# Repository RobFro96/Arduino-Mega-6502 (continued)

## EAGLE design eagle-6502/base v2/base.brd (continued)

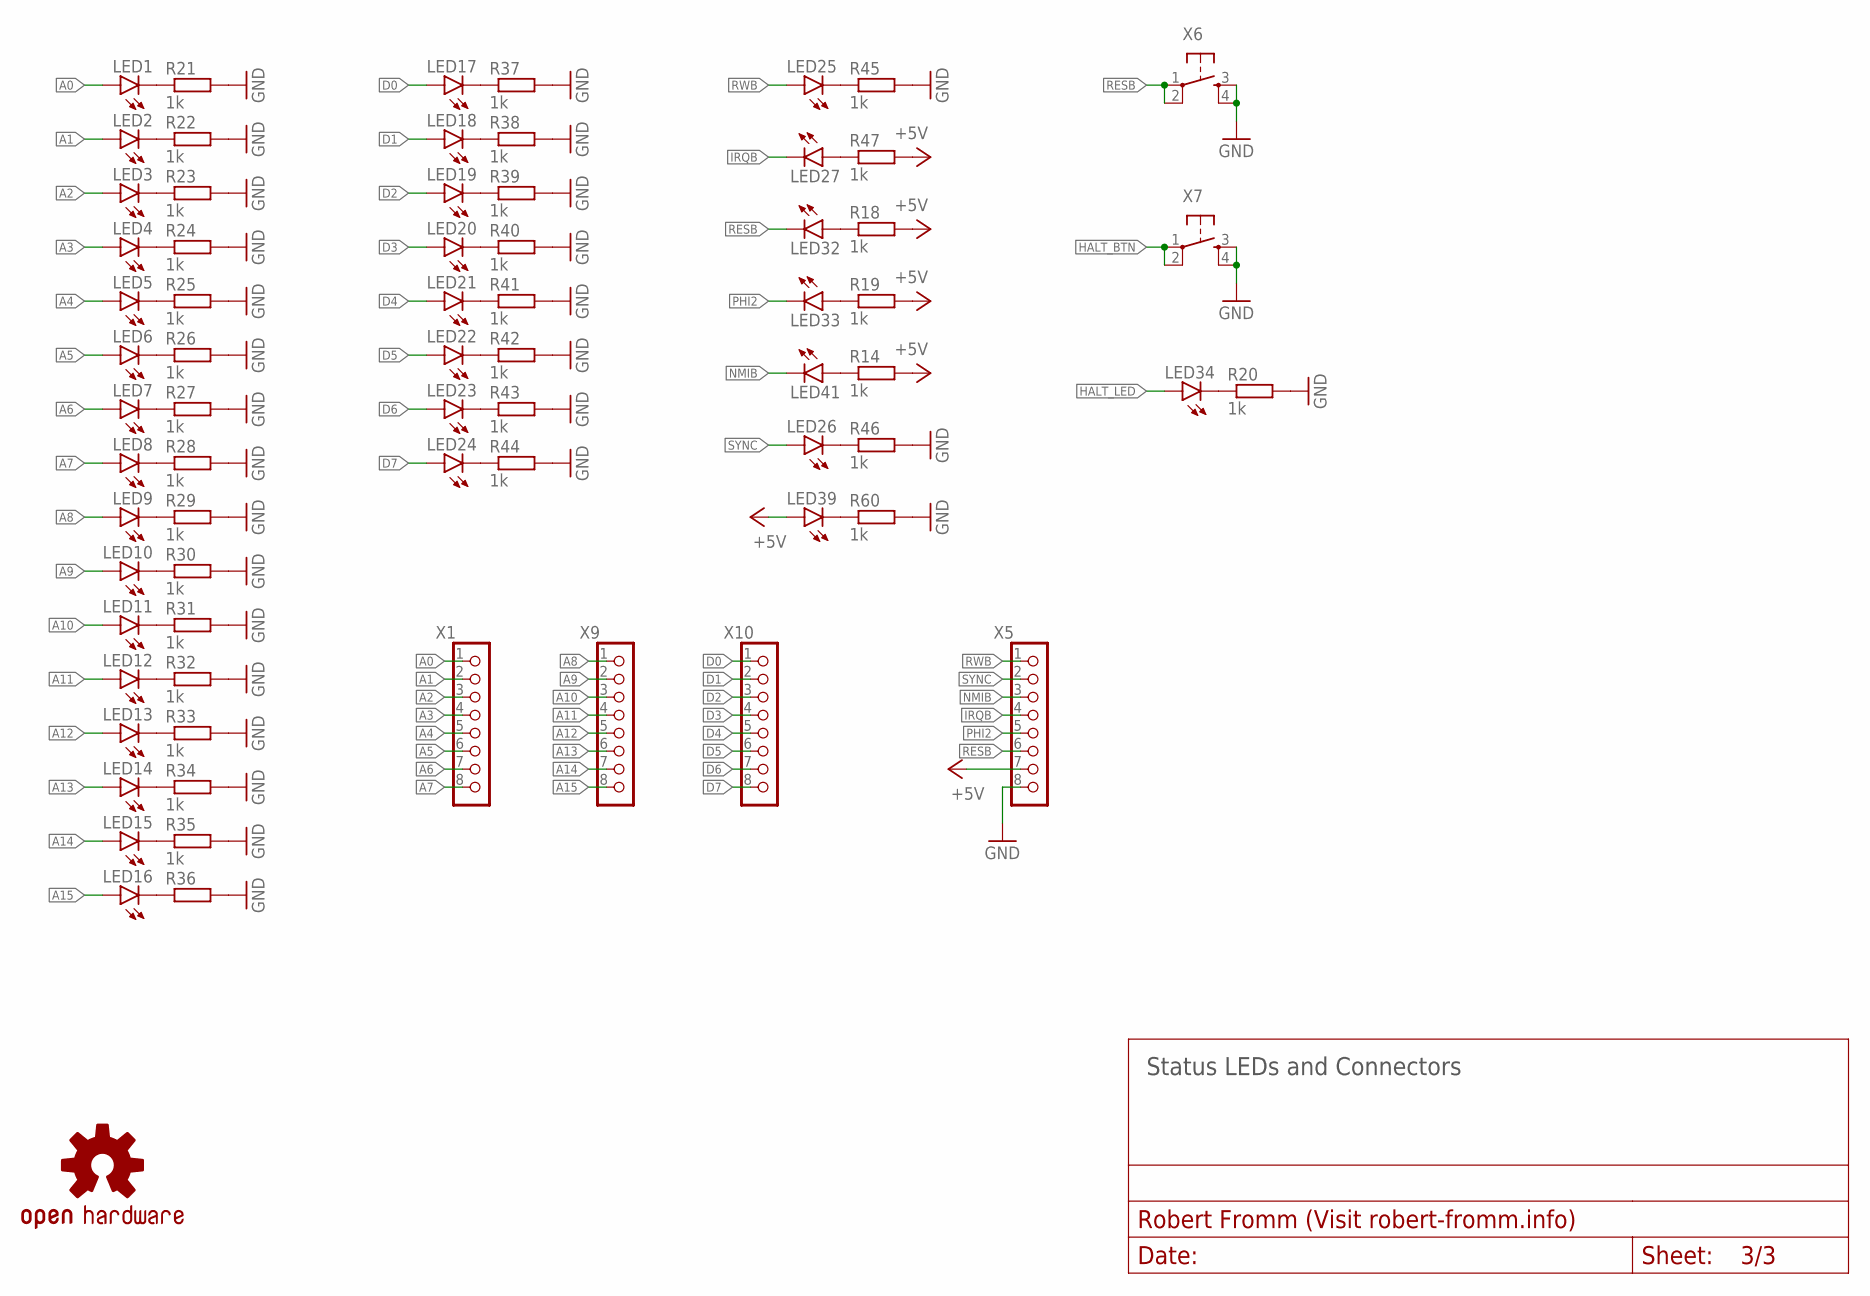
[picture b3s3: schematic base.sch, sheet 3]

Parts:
LED1, LED2, LED3, LED4, LED5, LED6, LED7, LED8, LED9, LED10, LED11, LED12, LED13, LED14, LED15, LED16, LED17, LED18, LED19, LED20, LED21, LED22, LED23, LED24, LED25, LED26, LED27, LED32, LED33, LED34, LED39, LED41: LEDSML0805; SML0805
LOGO1: OSHW-LOGOM; OSHW-LOGO-M
R14, R18, R19, R20, R21, R22, R23, R24, R25, R26, R27, R28, R29, R30, R31, R32, R33, R34, R35, R36, R37, R38, R39, R40, R41, R42, R43, R44, R45, R46, R47, R60: 1k; R0805
X1, X5, X9, X10: PINHD_8_RND; 1X08
X6, X7: TACT_SWITCH; TACTILE_SWITCH_PTH_6.0MM

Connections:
+5V: LED39.A, R14.2, R18.2, R19.2, R47.2, X5.7; also elsewhere on the board
A0: LED1.A, X1.1; also elsewhere on the board
A1: LED2.A, X1.2; also elsewhere on the board
A2: LED3.A, X1.3; also elsewhere on the board
A3: LED4.A, X1.4; also elsewhere on the board
A4: LED5.A, X1.5; also elsewhere on the board
A5: LED6.A, X1.6; also elsewhere on the board
A6: LED7.A, X1.7; also elsewhere on the board
A7: LED8.A, X1.8; also elsewhere on the board
A8: LED9.A, X9.1; also elsewhere on the board
A9: LED10.A, X9.2; also elsewhere on the board
A10: LED11.A, X9.3; also elsewhere on the board
A11: LED12.A, X9.4; also elsewhere on the board
A12: LED13.A, X9.5; also elsewhere on the board
A13: LED14.A, X9.6; also elsewhere on the board
A14: LED15.A, X9.7; also elsewhere on the board
A15: LED16.A, X9.8; also elsewhere on the board
D0: LED17.A, X10.1; also elsewhere on the board
D1: LED18.A, X10.2; also elsewhere on the board
D2: LED19.A, X10.3; also elsewhere on the board
D3: LED20.A, X10.4; also elsewhere on the board
D4: LED21.A, X10.5; also elsewhere on the board
D5: LED22.A, X10.6; also elsewhere on the board
D6: LED23.A, X10.7; also elsewhere on the board
D7: LED24.A, X10.8; also elsewhere on the board
GND: R20.2, R21.2, R22.2, R23.2, R24.2, R25.2, R26.2, R27.2, R28.2, R29.2, R30.2, R31.2, R32.2, R33.2, R34.2, R35.2, R36.2, R37.2, R38.2, R39.2, R40.2, R41.2, R42.2, R43.2, R44.2, R45.2, R46.2, R60.2, X5.8, X6.3, X6.4, X7.3, X7.4; also elsewhere on the board
HALT_BTN: X7.1, X7.2; also elsewhere on the board
HALT_LED: LED34.A; also elsewhere on the board
IRQB: LED27.C, X5.4; also elsewhere on the board
unnamed: LED41.A, R14.1
unnamed: LED1.C, R21.1
unnamed: LED2.C, R22.1
unnamed: LED3.C, R23.1
unnamed: LED4.C, R24.1
unnamed: LED5.C, R25.1
unnamed: LED6.C, R26.1
unnamed: LED7.C, R27.1
unnamed: LED8.C, R28.1
unnamed: LED9.C, R29.1
unnamed: LED10.C, R30.1
unnamed: LED11.C, R31.1
unnamed: LED12.C, R32.1
unnamed: LED13.C, R33.1
unnamed: LED14.C, R34.1
unnamed: LED15.C, R35.1
unnamed: LED16.C, R36.1
unnamed: LED17.C, R37.1
unnamed: LED18.C, R38.1
unnamed: LED19.C, R39.1
unnamed: LED20.C, R40.1
unnamed: LED21.C, R41.1
unnamed: LED22.C, R42.1
unnamed: LED23.C, R43.1
unnamed: LED24.C, R44.1
unnamed: LED25.C, R45.1
unnamed: LED26.C, R46.1
unnamed: LED27.A, R47.1
unnamed: LED39.C, R60.1
unnamed: LED32.A, R18.1
unnamed: LED33.A, R19.1
unnamed: LED34.C, R20.1
NMIB: LED41.C, X5.3; also elsewhere on the board
PHI2: LED33.C, X5.5; also elsewhere on the board
RESB: LED32.C, X5.6, X6.1, X6.2; also elsewhere on the board
RWB: LED25.A, X5.1; also elsewhere on the board
SYNC: LED26.A, X5.2; also elsewhere on the board

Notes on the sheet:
Status LEDs and Connectors

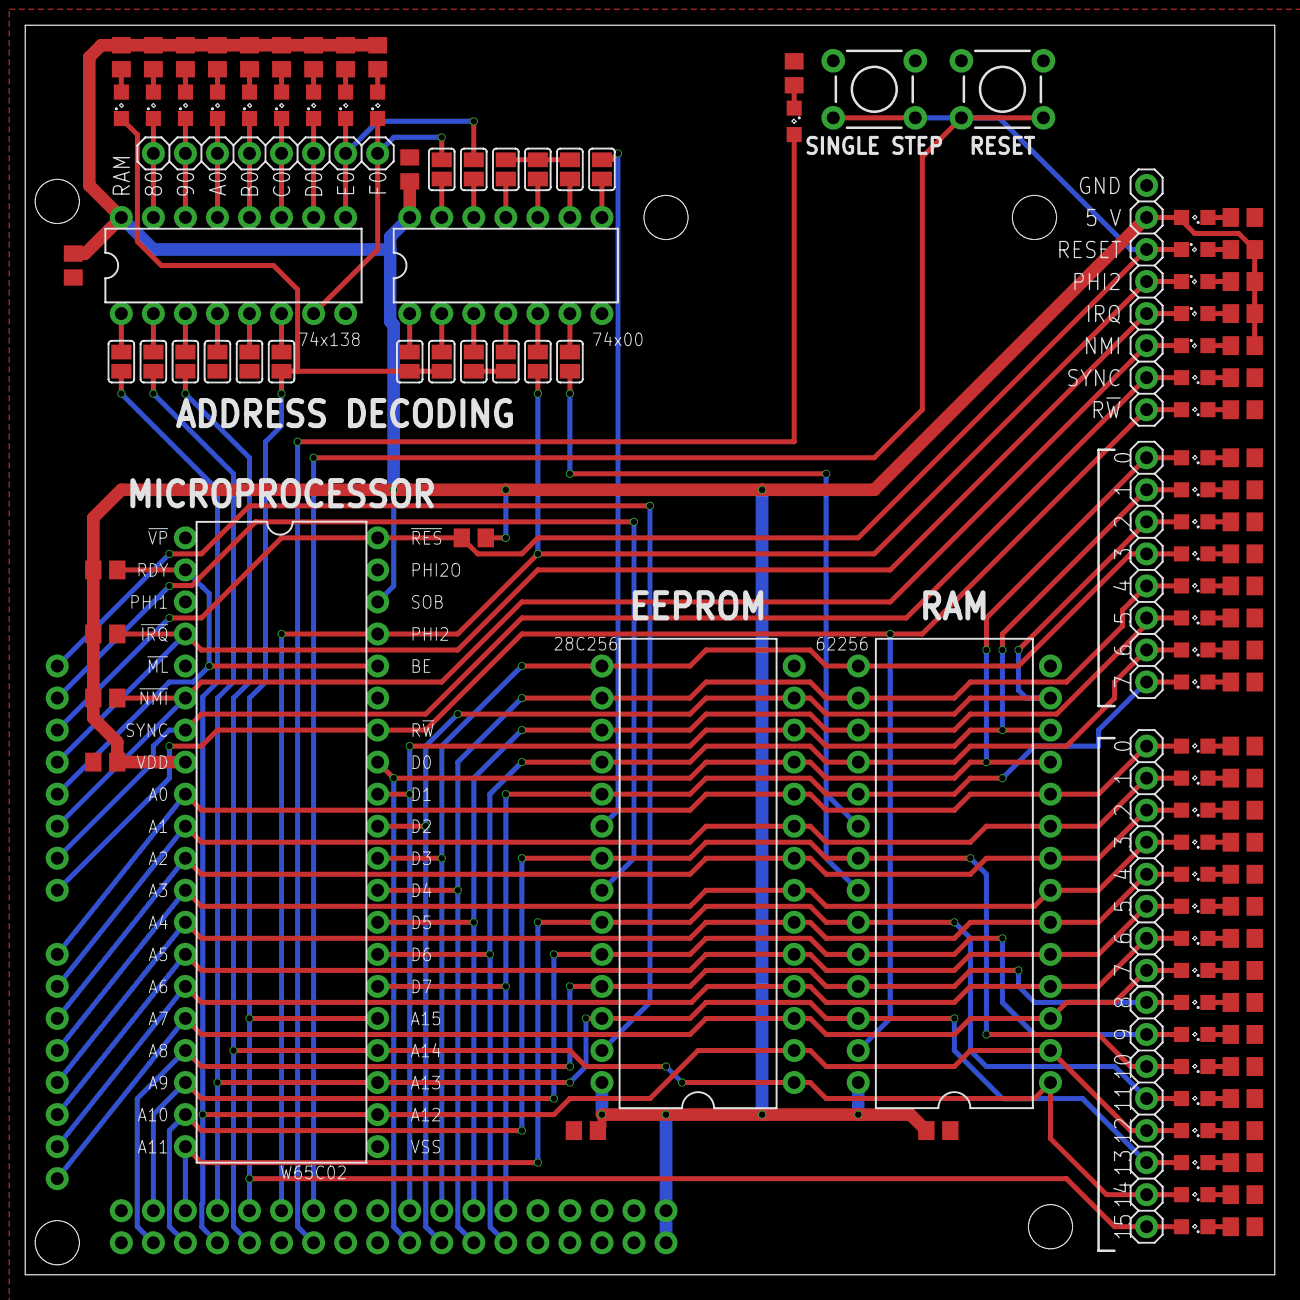
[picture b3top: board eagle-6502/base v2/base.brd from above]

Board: 2 copper layers, 99.1 x 99.1 mm, 123 parts (0 on the bottom side), 108 nets.

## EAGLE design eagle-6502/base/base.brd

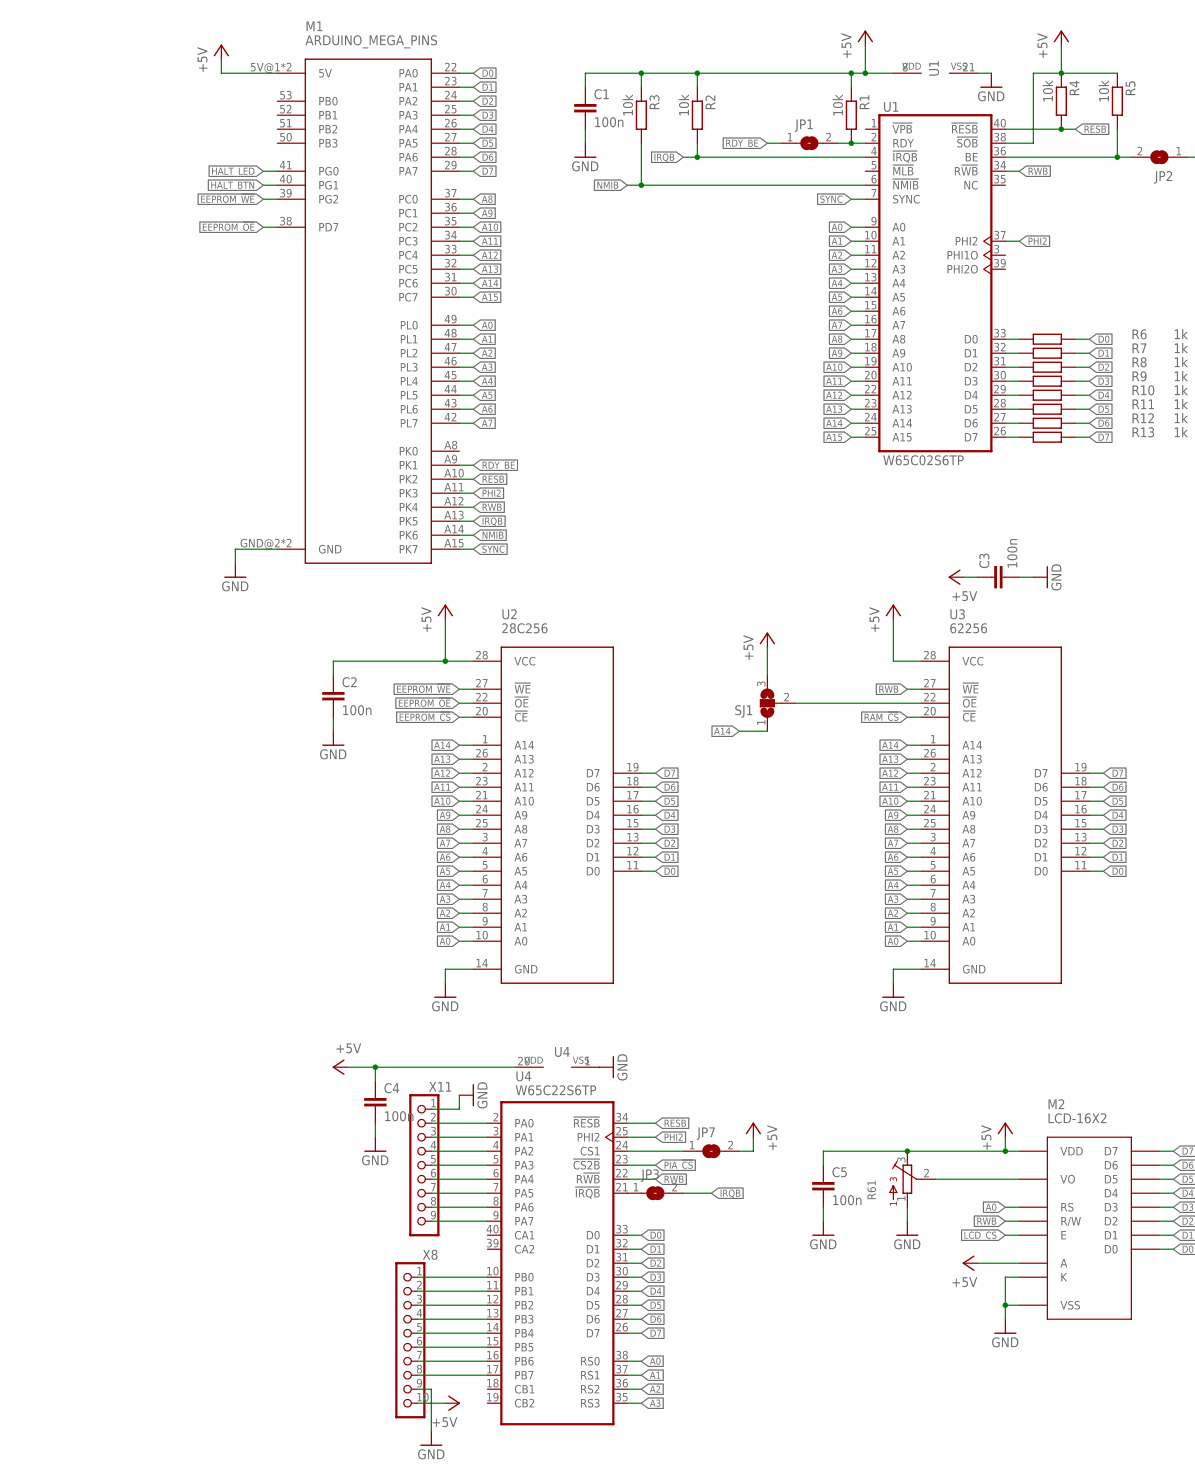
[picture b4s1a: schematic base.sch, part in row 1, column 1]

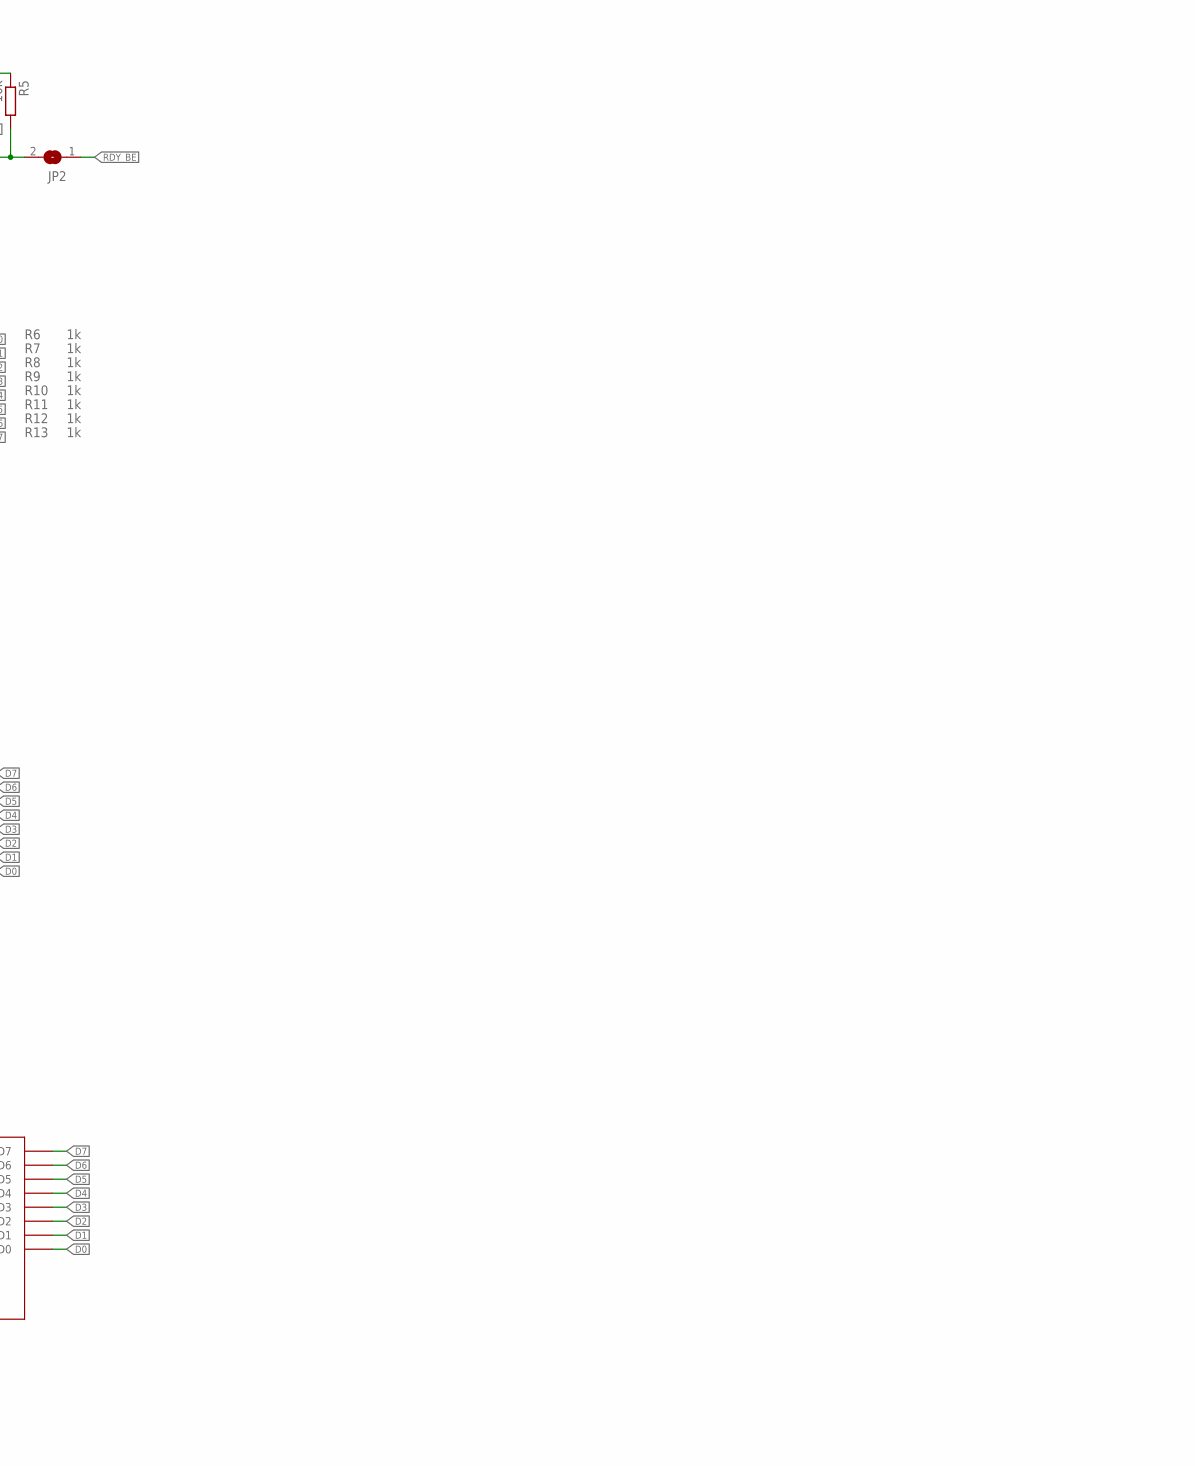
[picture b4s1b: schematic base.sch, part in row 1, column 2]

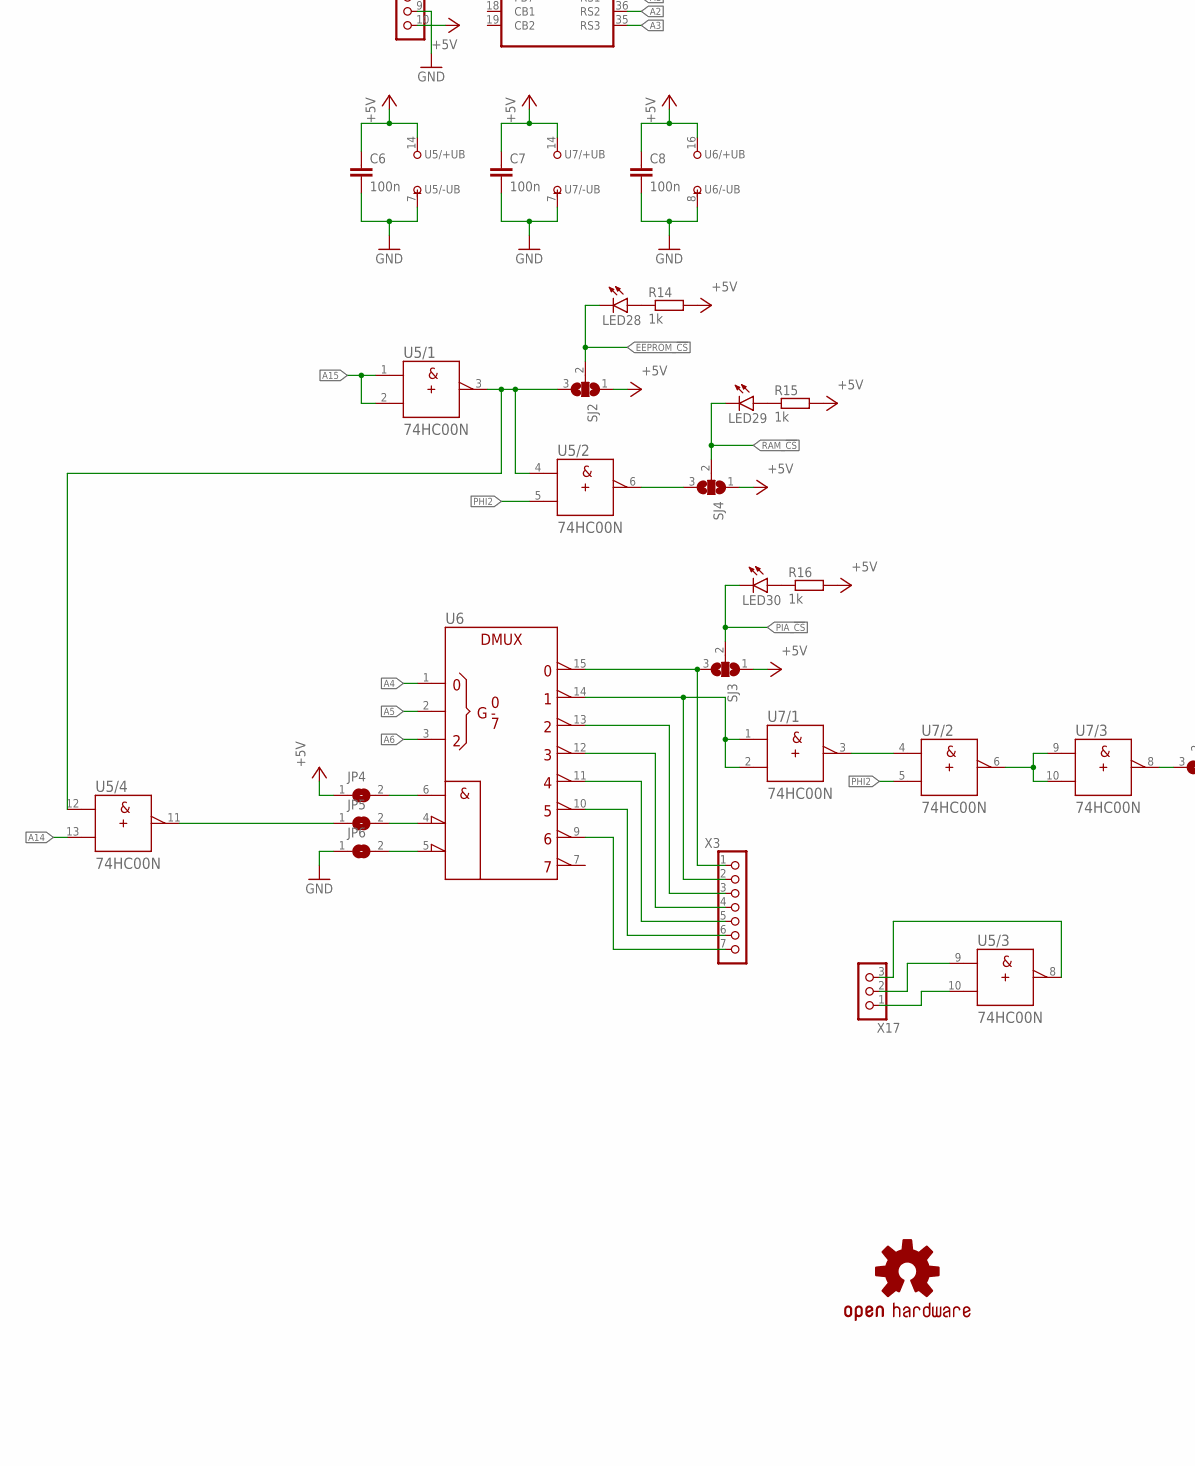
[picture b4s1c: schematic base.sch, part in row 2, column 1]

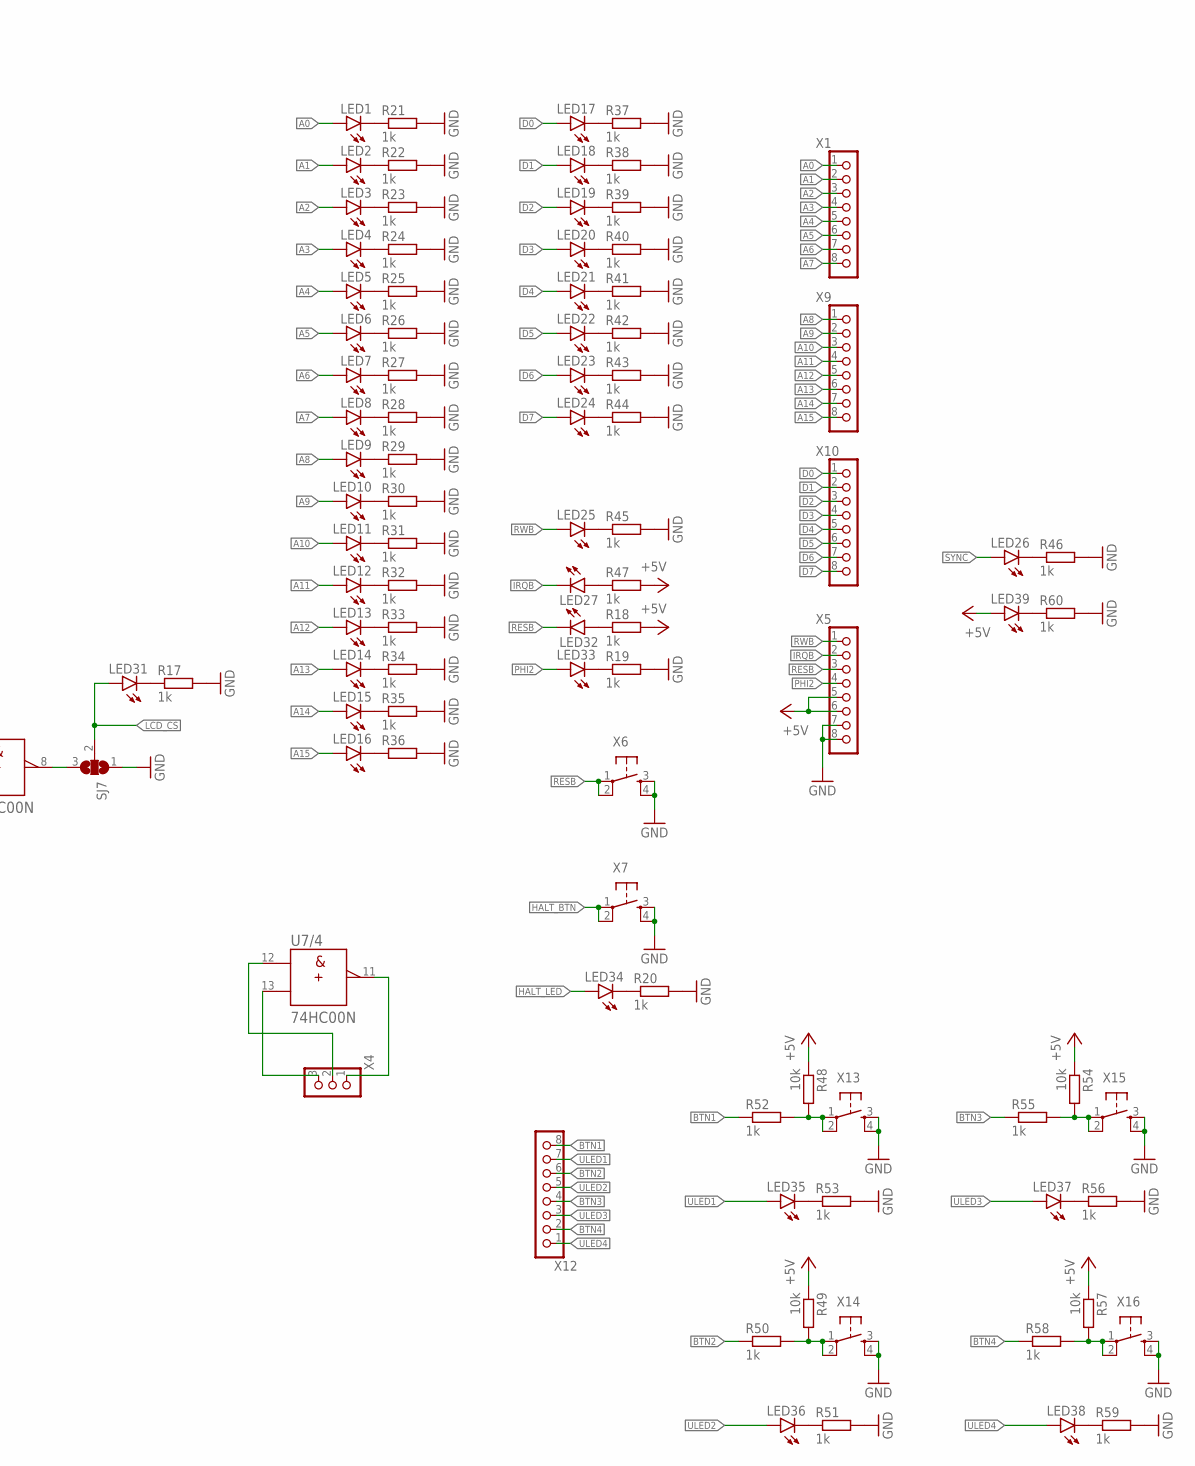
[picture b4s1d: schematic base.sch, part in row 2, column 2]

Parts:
C1, C2, C3, C4, C5, C6, C7, C8: 100n; C0805
JP1, JP2, JP3, JP4, JP5, JP6, JP7: SJ
LED1, LED2, LED3, LED4, LED5, LED6, LED7, LED8, LED9, LED10, LED11, LED12, LED13, LED14, LED15, LED16, LED17, LED18, LED19, LED20, LED21, LED22, LED23, LED24, LED25, LED26, LED27, LED28, LED29, LED30, LED31, LED32, LED33, LED34, LED35, LED36, LED37, LED38, LED39: LEDSML0805; SML0805
LOGO1: OSHW-LOGOM; OSHW-LOGO-M
M1: ARDUINO_MEGA_PINS
M2: LCD-16X2
R1, R2, R3, R4, R5, R48, R49, R54, R57: 10k; R0805
R6, R7, R8, R9, R10, R11, R12, R13, R14, R15, R16, R17, R18, R19, R20, R21, R22, R23, R24, R25, R26, R27, R28, R29, R30, R31, R32, R33, R34, R35, R36, R37, R38, R39, R40, R41, R42, R43, R44, R45, R46, R47, R50, R51, R52, R53, R55, R56, R58, R59, R60: 1k; R0805
R61: 3362P
SJ1, SJ2, SJ3, SJ4, SJ7: SJ2W; SJ_2
U1: W65C02S6TP; DIL40
U2: 28C256; DIL28-6
U3: 62256; DIL28-6
U4: W65C22S6TP; DIL40
U5, U7: 74HC00N; DIL14
U6: 74138N; DIL16
X1, X5, X9, X10, X12: PINHD_8_RND; 1X08
X3: PINHD_7_RND; 1X07
X4, X17: PINHD_3_RND; 1X03
X6, X7, X13, X14, X15, X16: TACT_SWITCH; TACTILE_SWITCH_PTH_6.0MM
X8: PINHD_10_RND; 1X10
X11: PINHD_9_RND; 1X09

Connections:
+5V: C1.1, C2.1, C3.1, C4.1, C5.1, C6.1, C7.1, C8.1, JP4.1, JP7.2, LED39.A, M1.5V@1 (5V), M1.5V@2 (5V), M2.2 (VDD), M2.15 (A), R1.1, R2.1, R3.1, R4.1, R5.1, R14.2, R15.2, R16.2, R18.2, R47.2, R48.1, R49.1, R54.1, R57.1, R61.3, SJ1.3, SJ2.1, SJ3.1, SJ4.1, U1.8 (VDD), U1.38 (!SOB), U2.28 (VCC), U3.28 (VCC), U4.20 (VDD), U5.14 (+UB), U6.16 (+UB), U7.14 (+UB), X5.5, X5.6, X8.10
A0: LED1.A, M1.49 (PL0), M2.4 (RS), U1.9 (A0), U2.10 (A0), U3.10 (A0), U4.38 (RS0), X1.1
A1: LED2.A, M1.48 (PL1), U1.10 (A1), U2.9 (A1), U3.9 (A1), U4.37 (RS1), X1.2
A2: LED3.A, M1.47 (PL2), U1.11 (A2), U2.8 (A2), U3.8 (A2), U4.36 (RS2), X1.3
A3: LED4.A, M1.46 (PL3), U1.12 (A3), U2.7 (A3), U3.7 (A3), U4.35 (RS3), X1.4
A4: LED5.A, M1.45 (PL4), U1.13 (A4), U2.6 (A4), U3.6 (A4), U6.1 (A), X1.5
A5: LED6.A, M1.44 (PL5), U1.14 (A5), U2.5 (A5), U3.5 (A5), U6.2 (B), X1.6
A6: LED7.A, M1.43 (PL6), U1.15 (A6), U2.4 (A6), U3.4 (A6), U6.3 (C), X1.7
A7: LED8.A, M1.42 (PL7), U1.16 (A7), U2.3 (A7), U3.3 (A7), X1.8
A8: LED9.A, M1.37 (PC0), U1.17 (A8), U2.25 (A8), U3.25 (A8), X9.1
A9: LED10.A, M1.36 (PC1), U1.18 (A9), U2.24 (A9), U3.24 (A9), X9.2
A10: LED11.A, M1.35 (PC2), U1.19 (A10), U2.21 (A10), U3.21 (A10), X9.3
A11: LED12.A, M1.34 (PC3), U1.20 (A11), U2.23 (A11), U3.23 (A11), X9.4
A12: LED13.A, M1.33 (PC4), U1.22 (A12), U2.2 (A12), U3.2 (A12), X9.5
A13: LED14.A, M1.32 (PC5), U1.23 (A13), U2.26 (A13), U3.26 (A13), X9.6
A14: LED15.A, M1.31 (PC6), SJ1.1, U1.24 (A14), U2.1 (A14), U3.1 (A14), U5.13 (B), X9.7
A15: LED16.A, M1.30 (PC7), U1.25 (A15), U5.1 (A), U5.2 (B), X9.8
BE: JP2.2, R5.2, U1.36 (BE)
BTN1: R52.1, X12.8
BTN2: R50.1, X12.6
BTN3: R55.1, X12.4
BTN4: R58.1, X12.2
D0: LED17.A, M1.22 (PA0), M2.7 (D0), R6.2, U2.11 (D0), U3.11 (D0), U4.33 (D0), X10.1
D1: LED18.A, M1.23 (PA1), M2.8 (D1), R7.2, U2.12 (D1), U3.12 (D1), U4.32 (D1), X10.2
D2: LED19.A, M1.24 (PA2), M2.9 (D2), R8.2, U2.13 (D2), U3.13 (D2), U4.31 (D2), X10.3
D3: LED20.A, M1.25 (PA3), M2.10 (D3), R9.2, U2.15 (D3), U3.15 (D3), U4.30 (D3), X10.4
D4: LED21.A, M1.26 (PA4), M2.11 (D4), R10.2, U2.16 (D4), U3.16 (D4), U4.29 (D4), X10.5
D5: LED22.A, M1.27 (PA5), M2.12 (D5), R11.2, U2.17 (D5), U3.17 (D5), U4.28 (D5), X10.6
D6: LED23.A, M1.28 (PA6), M2.13 (D6), R12.2, U2.18 (D6), U3.18 (D6), U4.27 (D6), X10.7
D7: LED24.A, M1.29 (PA7), M2.14 (D7), R13.2, U2.19 (D7), U3.19 (D7), U4.26 (D7), X10.8
EEPROM_!CS: LED28.C, SJ2.2, U2.20 (!CE)
EEPROM_!OE: M1.38 (PD7), U2.22 (!OE)
EEPROM_!WE: M1.39 (PG2), U2.27 (!WE)
GND: C1.2, C2.2, C3.2, C4.2, C5.2, C6.2, C7.2, C8.2, JP6.1, M1.GND@2 (GND), M1.GND@3 (GND), M2.1 (VSS), M2.16 (K), R17.2, R19.2, R20.2, R21.2, R22.2, R23.2, R24.2, R25.2, R26.2, R27.2, R28.2, R29.2, R30.2, R31.2, R32.2, R33.2, R34.2, R35.2, R36.2, R37.2, R38.2, R39.2, R40.2, R41.2, R42.2, R43.2, R44.2, R45.2, R46.2, R51.2, R53.2, R56.2, R59.2, R60.2, R61.1, SJ7.1, U1.21 (VSS), U2.14 (GND), U3.14 (GND), U4.1 (VSS), U5.7 (-UB), U6.8 (-UB), U7.7 (-UB), X5.7, X5.8, X6.3, X6.4, X7.3, X7.4, X8.9, X11.1, X13.3, X13.4, X14.3, X14.4, X15.3, X15.4, X16.3, X16.4
HALT_BTN: M1.40 (PG1), X7.1, X7.2
HALT_LED: LED34.A, M1.41 (PG0)
IRQB: JP3.2, LED27.C, M1.A13 (PK5), R2.2, U1.4 (!IRQB), X5.2
LCD_CS: LED31.A, M2.6 (E), SJ7.2
unnamed: R6.1, U1.33 (D0)
unnamed: R7.1, U1.32 (D1)
unnamed: R8.1, U1.31 (D2)
unnamed: R9.1, U1.30 (D3)
unnamed: R10.1, U1.29 (D4)
unnamed: R11.1, U1.28 (D5)
unnamed: R12.1, U1.27 (D6)
unnamed: R13.1, U1.26 (D7)
unnamed: U5.8 (Y), X17.3
unnamed: U5.9 (A), X17.2
unnamed: SJ1.2, U3.22 (!OE)
unnamed: SJ2.3, U5.3 (Y), U5.4 (A), U5.12 (A)
unnamed: SJ4.3, U5.6 (Y)
unnamed: SJ3.3, U6.15 (Y0), X3.1
unnamed: JP4.2, U6.6 (G1)
unnamed: JP5.1, U5.11 (Y)
unnamed: JP6.2, U6.5 (!G2B)
unnamed: U6.14 (Y1), U7.1 (A), U7.2 (B), X3.2
unnamed: U7.3 (Y), U7.4 (A)
unnamed: U7.6 (Y), U7.9 (A), U7.10 (B)
unnamed: SJ7.3, U7.8 (Y)
unnamed: LED1.C, R21.1
unnamed: LED2.C, R22.1
unnamed: LED3.C, R23.1
unnamed: LED4.C, R24.1
unnamed: LED5.C, R25.1
unnamed: LED6.C, R26.1
unnamed: LED7.C, R27.1
unnamed: LED8.C, R28.1
unnamed: LED9.C, R29.1
unnamed: LED10.C, R30.1
unnamed: LED11.C, R31.1
unnamed: LED12.C, R32.1
unnamed: LED13.C, R33.1
unnamed: LED14.C, R34.1
unnamed: LED15.C, R35.1
unnamed: LED16.C, R36.1
unnamed: LED17.C, R37.1
unnamed: LED18.C, R38.1
unnamed: LED19.C, R39.1
unnamed: LED20.C, R40.1
unnamed: LED21.C, R41.1
unnamed: LED22.C, R42.1
unnamed: LED23.C, R43.1
unnamed: LED24.C, R44.1
unnamed: LED25.C, R45.1
unnamed: LED26.C, R46.1
unnamed: LED27.A, R47.1
unnamed: LED28.A, R14.1
unnamed: LED29.A, R15.1
unnamed: LED30.A, R16.1
unnamed: U5.10 (B), X17.1
unnamed: JP5.2, U6.4 (!G2A)
unnamed: LED39.C, R60.1
unnamed: JP3.1, U4.21 (!IRQB)
unnamed: U6.12 (Y3), X3.4
unnamed: U6.11 (Y4), X3.5
unnamed: U6.13 (Y2), X3.3
unnamed: U6.10 (Y5), X3.6
unnamed: U6.9 (Y6), X3.7
unnamed: LED31.C, R17.1
unnamed: U7.11 (Y), X4.1
unnamed: U7.12 (A), X4.2
unnamed: U7.13 (B), X4.3
unnamed: LED32.A, R18.1
unnamed: LED33.C, R19.1
unnamed: LED34.C, R20.1
unnamed: U4.2 (PA0), X11.2
unnamed: U4.3 (PA1), X11.3
unnamed: U4.4 (PA2), X11.4
unnamed: U4.5 (PA3), X11.5
unnamed: U4.6 (PA4), X11.6
unnamed: U4.7 (PA5), X11.7
unnamed: U4.8 (PA6), X11.8
unnamed: U4.9 (PA7), X11.9
unnamed: U4.10 (PB0), X8.1
unnamed: U4.11 (PB1), X8.2
unnamed: U4.12 (PB2), X8.3
unnamed: U4.13 (PB3), X8.4
unnamed: U4.14 (PB4), X8.5
unnamed: U4.15 (PB5), X8.6
unnamed: U4.16 (PB6), X8.7
unnamed: U4.17 (PB7), X8.8
unnamed: R48.2, R52.2, X13.1, X13.2
unnamed: LED35.C, R53.1
unnamed: R49.2, R50.2, X14.1, X14.2
unnamed: LED36.C, R51.1
unnamed: R54.2, R55.2, X15.1, X15.2
unnamed: LED37.C, R56.1
unnamed: R57.2, R58.2, X16.1, X16.2
unnamed: JP7.1, U4.24 (CS1)
unnamed: M2.3 (VO), R61.2
unnamed: LED38.C, R59.1
NMIB: M1.A14 (PK6), R3.2, U1.6 (!NMIB)
PHI2: LED33.A, M1.A11 (PK3), U1.37 (PHI2), U4.25 (PHI2), U5.5 (B), U7.5 (B), X5.4
PIA_!CS: LED30.C, SJ3.2, U4.23 (!CS2B)
RAM_!CS: LED29.C, SJ4.2, U3.20 (!CE)
RDY: JP1.2, R1.2, U1.2 (RDY)
RDY_BE: JP1.1, JP2.1, M1.A9 (PK1)
RESB: LED32.C, M1.A10 (PK2), R4.2, U1.40 (!RESB), U4.34 (!RESB), X5.3, X6.1, X6.2
RWB: LED25.A, M1.A12 (PK4), M2.5 (R/W), U1.34 (R!WB), U3.27 (!WE), U4.22 (R!WB), X5.1
SYNC: LED26.A, M1.A15 (PK7), U1.7 (SYNC)
ULED1: LED35.A, X12.7
ULED2: LED36.A, X12.5
ULED3: LED37.A, X12.3
ULED4: LED38.A, X12.1

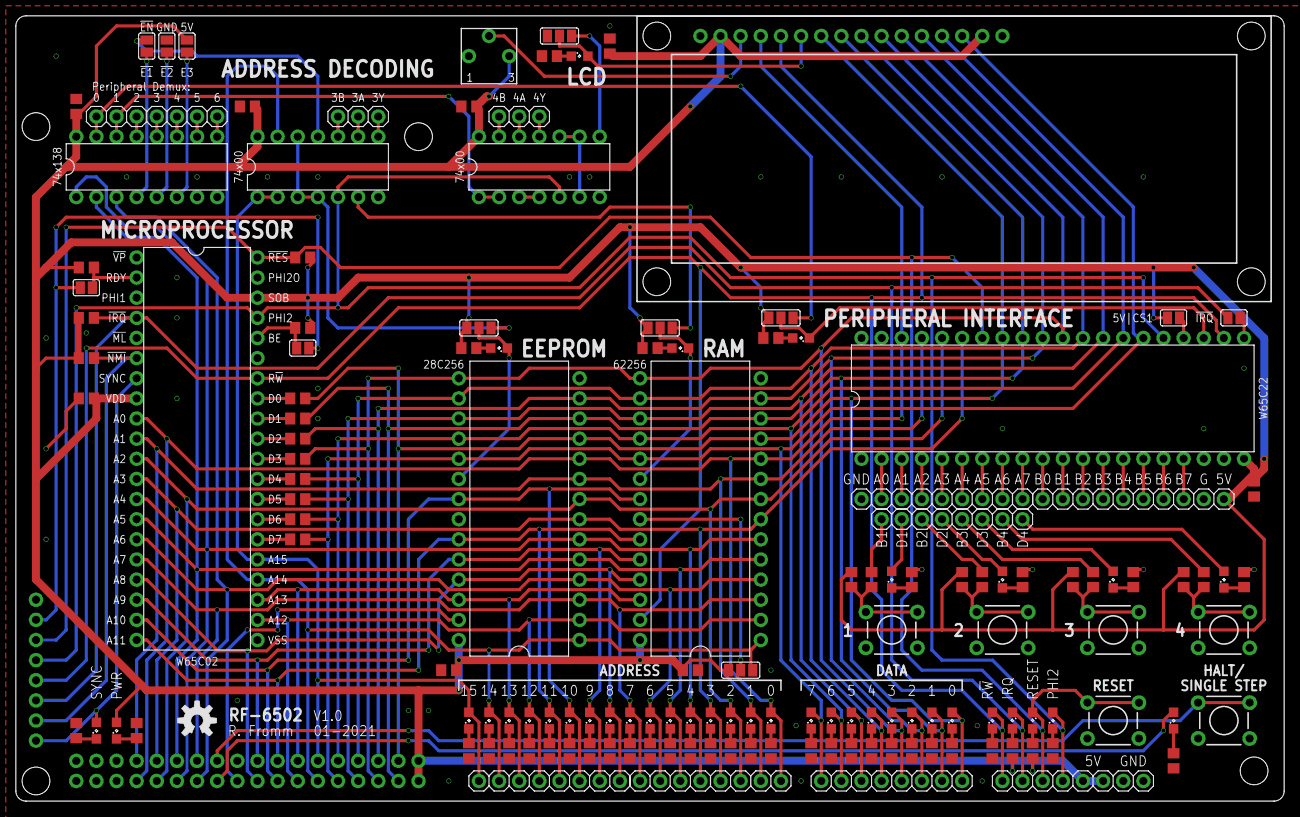
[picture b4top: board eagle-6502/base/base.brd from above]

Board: 2 copper layers, 160.0 x 99.1 mm, 146 parts (0 on the bottom side), 144 nets.

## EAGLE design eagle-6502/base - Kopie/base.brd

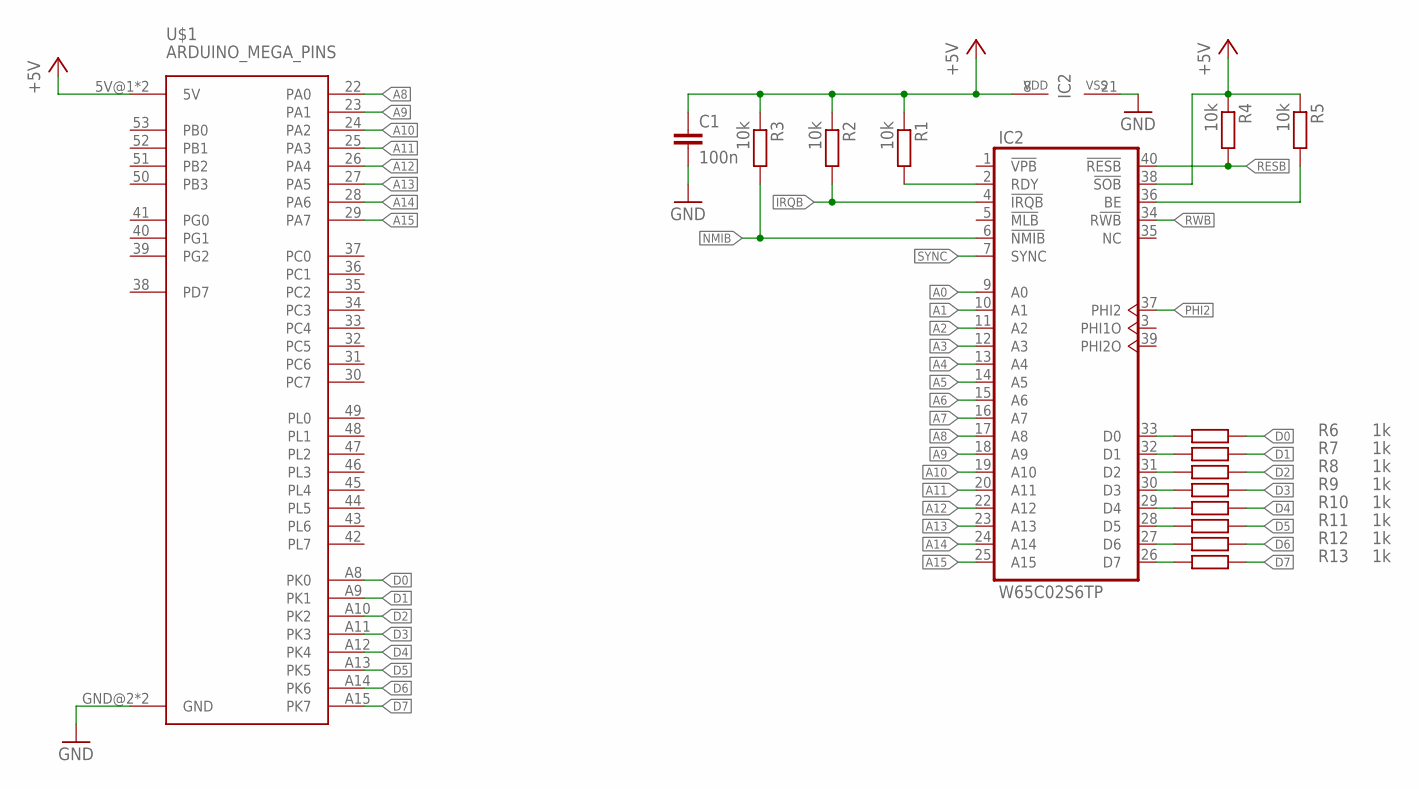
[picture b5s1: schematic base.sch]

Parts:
C1: 100n; C0805
IC2: W65C02S6TP; DIL40
R1, R2, R3, R4, R5: 10k; R0805
R6, R7, R8, R9, R10, R11, R12, R13: 1k; R0805
U$1: ARDUINO_MEGA_PINS

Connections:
+5V: C1.1, IC2.8 (VDD), IC2.38 (!SOB), R1.1, R2.1, R3.1, R4.1, R5.1, U$1.5V@1 (5V), U$1.5V@2 (5V)
A0: IC2.9 (A0)
A1: IC2.10 (A1)
A2: IC2.11 (A2)
A3: IC2.12 (A3)
A4: IC2.13 (A4)
A5: IC2.14 (A5)
A6: IC2.15 (A6)
A7: IC2.16 (A7)
A8: IC2.17 (A8), U$1.22 (PA0)
A9: IC2.18 (A9), U$1.23 (PA1)
A10: IC2.19 (A10), U$1.24 (PA2)
A11: IC2.20 (A11), U$1.25 (PA3)
A12: IC2.22 (A12), U$1.26 (PA4)
A13: IC2.23 (A13), U$1.27 (PA5)
A14: IC2.24 (A14), U$1.28 (PA6)
A15: IC2.25 (A15), U$1.29 (PA7)
BE: IC2.36 (BE), R5.2
D0: R6.2, U$1.A8 (PK0)
D1: R7.2, U$1.A9 (PK1)
D2: R8.2, U$1.A10 (PK2)
D3: R9.2, U$1.A11 (PK3)
D4: R10.2, U$1.A12 (PK4)
D5: R11.2, U$1.A13 (PK5)
D6: R12.2, U$1.A14 (PK6)
D7: R13.2, U$1.A15 (PK7)
GND: C1.2, IC2.21 (VSS), U$1.GND@2 (GND), U$1.GND@3 (GND)
IRQB: IC2.4 (!IRQB), R2.2
unnamed: IC2.33 (D0), R6.1
unnamed: IC2.32 (D1), R7.1
unnamed: IC2.31 (D2), R8.1
unnamed: IC2.30 (D3), R9.1
unnamed: IC2.29 (D4), R10.1
unnamed: IC2.28 (D5), R11.1
unnamed: IC2.27 (D6), R12.1
unnamed: IC2.26 (D7), R13.1
NMIB: IC2.6 (!NMIB), R3.2
PHI2: IC2.37 (PHI2)
RDY: IC2.2 (RDY), R1.2
RESB: IC2.40 (!RESB), R4.2
RWB: IC2.34 (R!WB)
SYNC: IC2.7 (SYNC)

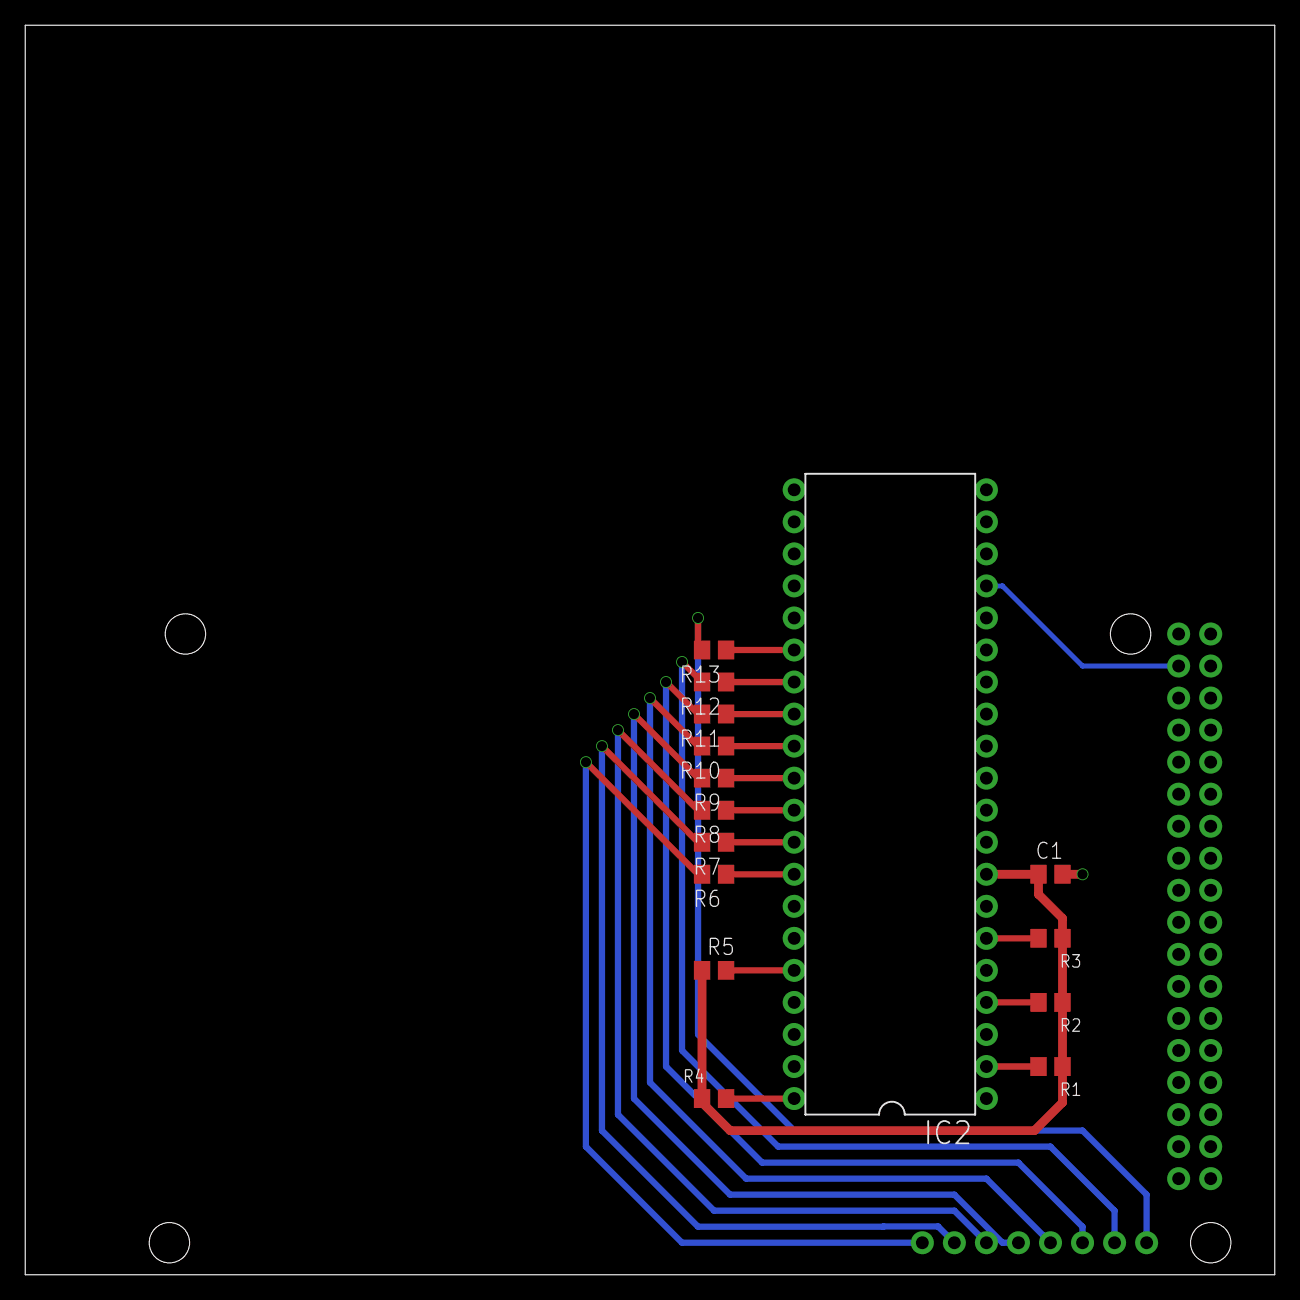
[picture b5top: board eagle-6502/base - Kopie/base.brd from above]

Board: 2 copper layers, 99.1 x 99.1 mm, 16 parts (0 on the bottom side), 31 nets.
